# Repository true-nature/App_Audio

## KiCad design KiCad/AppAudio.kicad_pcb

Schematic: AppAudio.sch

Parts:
BT1: Battery; B02B-XASK-1
C1, C6: 22u; C_Radial_D6.3_L11.2_P2.5
C2: 0.1u; C_Rect_L4_W2.5_P2.5
C3: 220u; C_Radial_D6.3_L11.2_P2.5
C4: 3300p; C_Rect_L4_W2.5_P2.5
C5: 1000p; C_Rect_L4_W2.5_P2.5
C7: 1u; C_Rect_L4_W2.5_P2.5
D1: Led_x2; LED-3MM
MIC1: MIC_ELECTRET; DB-C9767
P1: WRITER-VCC; WRITE-7P
Q1: Q_NMOS_SGD; EMT3
R1, R2, R6: 10k; R_0603_HandSoldering
R3, R4, R10, R13, R14, R15, R16, R17: 510; R_0603_HandSoldering
R5: 57k; R_0603_HandSoldering
R7, R8, R9: 22k; R_0603_HandSoldering
R11: 1M; Resistor_Horizontal_RM10mm
R12: 100k; Resistor_Horizontal_RM10mm
SP1: SPEAKER; B02B-XASK-1
SW1: SW_PUSH; TVGP01-G73BB
SW2: SW_PUSH; JB-15HFBP2
U1: TWE_LITE_SMD; TWE-001L-NC7
U2: NJM13404; DIP-8_W7.62mm
U3: HT82V739; DIP-8_W7.62mm
VR1: 50k; RV-3362P
VR2: 1k; RV-3362P

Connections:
/Aud_In: C6.1, U3.2
/CE#: U1.11, U3.5
/CFG: P1.6, U1.12
/OUTN: SP1.2, U3.1
/OUTP: SP1.1, U3.7
/PRG: P1.3, U1.2
/RST: P1.1, U1.21
/RXD: P1.2, U1.9
/TXD: P1.4, U1.8
/VREF: C7.2, U3.3
GND: BT1.2, C3.2, C7.1, P1.5, Q1.1, R11.2, R13.2, SW1.2, SW2.2, U1.20, U3.4
unnamed: C1.1, MIC1.1, R1.2
unnamed: C1.2, R2.2
unnamed: C4.1, R9.2, U2.6 (-), U2.7
unnamed: C4.2, R7.1, R8.2
unnamed: C5.1, R8.1, U2.5 (+)
unnamed: C6.2, R9.1
unnamed: D1.1, U1.3
unnamed: D1.2, R13.1
unnamed: D1.3, U1.4
unnamed: Q1.2, R10.2, R11.1
unnamed: R2.1, R5.2, U2.2 (-)
unnamed: R3.2, R4.1
unnamed: R5.1, VR1.1
unnamed: R6.1, VR1.3
unnamed: R7.2, VR2.2
unnamed: R10.1, U1.6
unnamed: R14.1, R15.2, U2.3 (+)
unnamed: R3.1, R14.2
unnamed: R15.1, R16.2
unnamed: R16.1, R17.2
unnamed: SW1.1, U1.13
unnamed: SW2.1, U1.15
unnamed: U1.7, VR2.3
unnamed: U1.22, U2.1, VR1.2
VCC: BT1.1, C2.2, C3.1, R1.1, R12.1, R17.1, U1.5, U1.23, U1.24, U1.25, U2.8 (V+), U3.8
VSS: C2.1, C5.2, MIC1.2, Q1.3, R4.2, R6.2, R12.2, U2.4 (V-), VR2.1

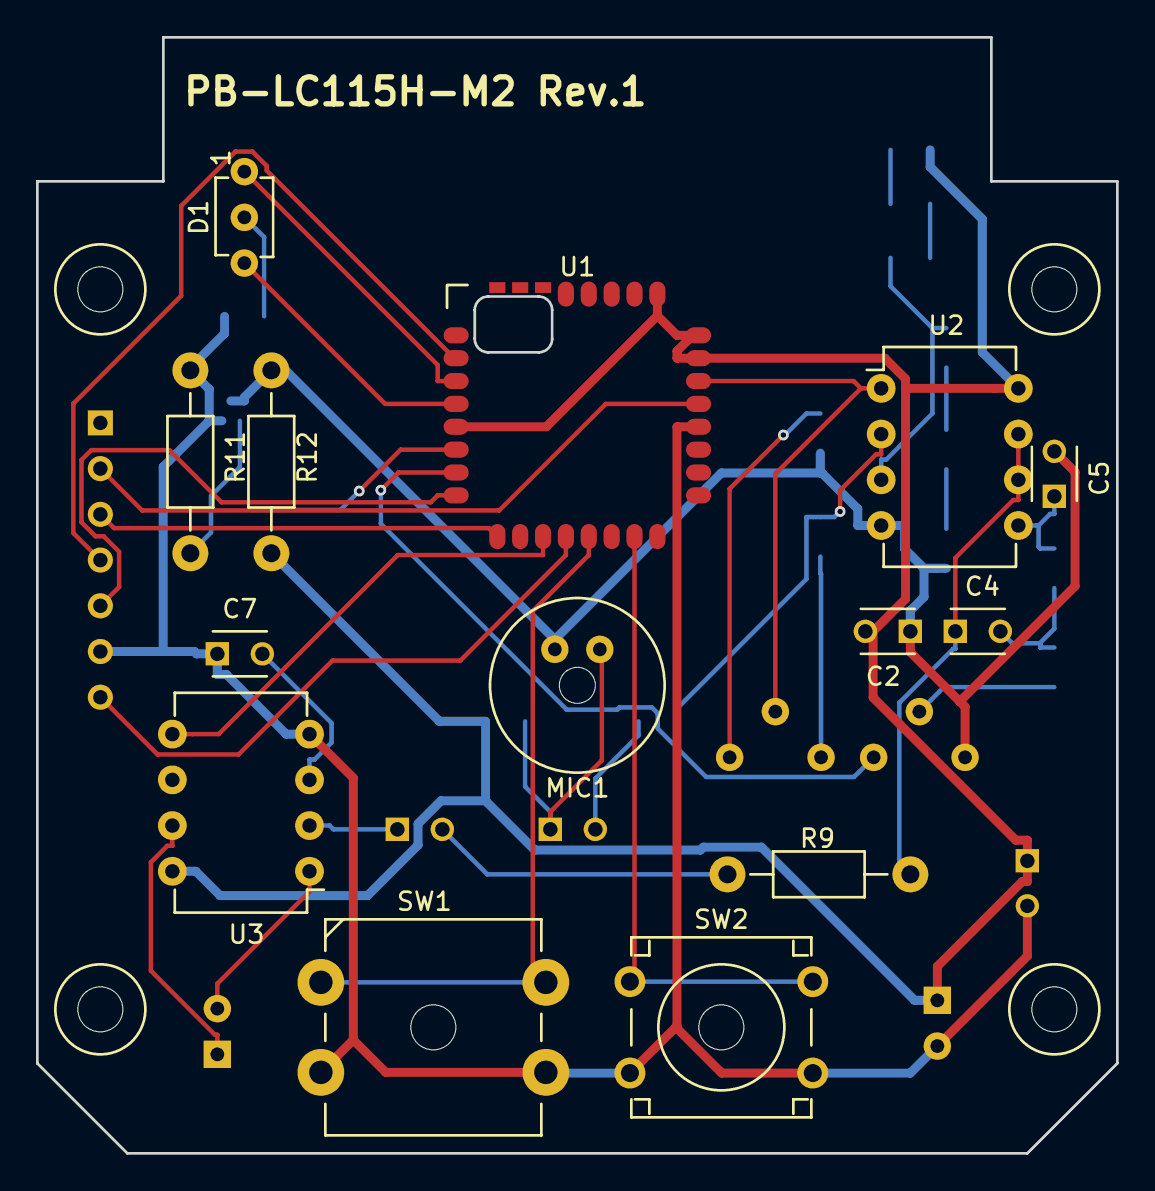
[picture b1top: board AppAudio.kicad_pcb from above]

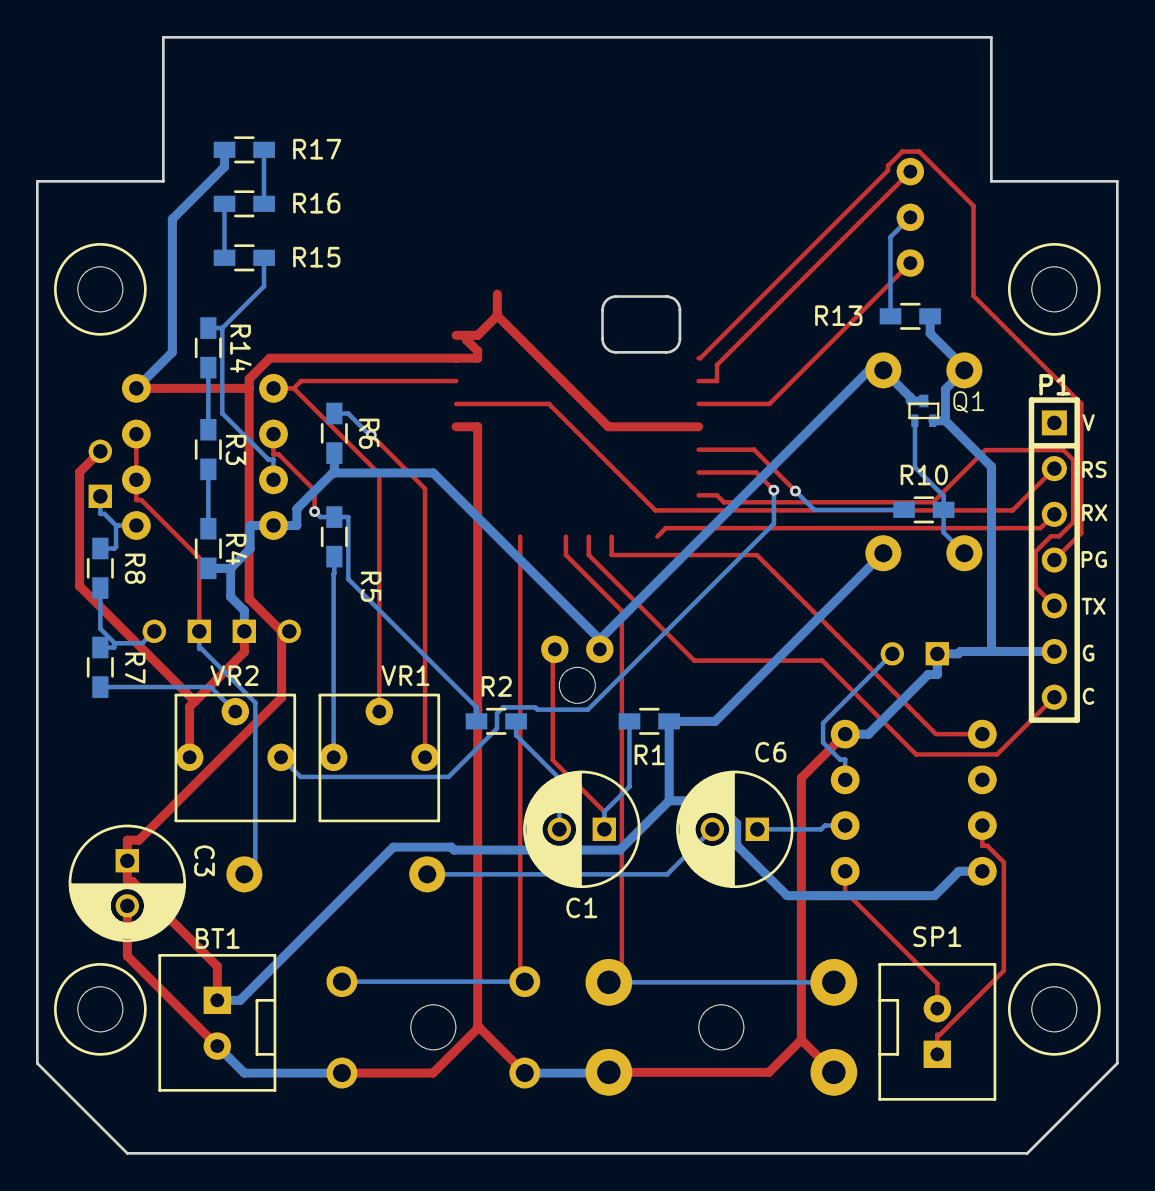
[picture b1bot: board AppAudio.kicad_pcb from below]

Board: 2 copper layers, 60.0 x 62.0 mm, 38 parts (23 on the bottom side), 37 nets.

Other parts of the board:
PB1: PB-LC115H-M2; PCB-LC115H

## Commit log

2016-04-19 Imported App_Audio project.
2016-04-19 Created KiCad project.
2016-04-19 Writing a schematic diagram.
2016-04-21 PCB layout in progress.
2016-04-22 Swapped TX and RX.
2016-05-01 PCB design in progress.
2016-05-01 Fixed wires.
2016-05-01 PCB layout has done.
2016-05-01 Relocated.
2016-05-02 Changed the footprint of the LED.
2016-05-05 Added the 3d model of the speaker.
2016-05-06 Replaced the footprint of SW2.
2016-05-06 Removed the net file.
2016-05-06 Implement interval sleep mode.
2016-05-06 Connect CE# to DO3.
2016-05-07 Changed analog input from ADC1 to ADC2 for wiring.
2016-05-07 Swapped DO3 and DO4. Assign CE# to DO4.
2016-05-08 Replaced some SMD registers.
2016-05-08 Assign LED1 as TX indicator.
2016-05-27 Implemented but not tested yet.
2016-06-04 Auto pairing worked correctly.
2016-06-05 Enable speaker amplifier slowly to avoid inrush noise.
2016-06-08 Use MEMS mic and passive LPF.
2016-06-08 Changed idle timer from E_EVENT_APP_TICK_A to E_EVENT_TICK_TIMER.
2016-06-08 Changed default sleep duration (600ms).
2018-03-11 Migrating to KiCad 5.0
2018-03-11 Add static modifier to a private function
